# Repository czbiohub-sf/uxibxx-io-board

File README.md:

# uxibxx-io-board
## Introduction
This repository contains the hardware design data, firmware and a Python driver implementation for the UXIB*xx* "family" of digital I/O board~~s~~. This project is intended to provide minimum-friction tools for interfacing Python code to electrical stuff (turning loads on and off, reading switches, etc) in laboratory automation projects.

Currently the device "family" consists of a single example, UXIB-DN12, designed to control a bank of 12 loads such as solenoid valves.

## Directory contents
- `driver/` contains the `uxibxx` Python package used to control UXIB*xx* devices
- `firmware/` contains the source code for the AVR firmware
- `pcb/` contains the KiCAD EDA project files for the UXIB-DN12 PCB

## Getting started
If starting with an already-made UXIB*xx* device, just install the included `uxibxx` package and review the associated API documentation. No extra system-level driver is required on Windows, MacOS or Linux.

See the `README.md` in each subdirectory for further information.

## Licenses
Software source code is licensed under the BSD 3-Clause License. Hardware design files are licensed under CERN-OHL-W.
See the `LICENSE` file in each subdirectory for a copy of the applicable license terms.

## Support
This project is maintained by Greg Courville of the Bioengineering Platform at Chan Zuckerberg Biohub San Francisco.

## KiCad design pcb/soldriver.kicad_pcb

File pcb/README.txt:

This directory has KiCAD 8 source files and other documentation for the UXIB-DN12 valve/relay controller board:

soldriver_sch.pdf            Printable UXIB-DN12 schematic
soldrive_assembly_front.pdf  UXIB-DN12 component placement drawing, front side
soldrive_assembly_back.pdf   UXIB-DN12 component placement drawing, rear side

soldriver.kicad_pro          UXIB-DN12 KiCAD 8 project file
soldriver.kicad_sch          UXIB-DN12 schematic
soldriver.kicad_pcb          UXIB-DN12 PCB layout
footprints.pretty/           Project footprint library
sym/                         Project symbol library

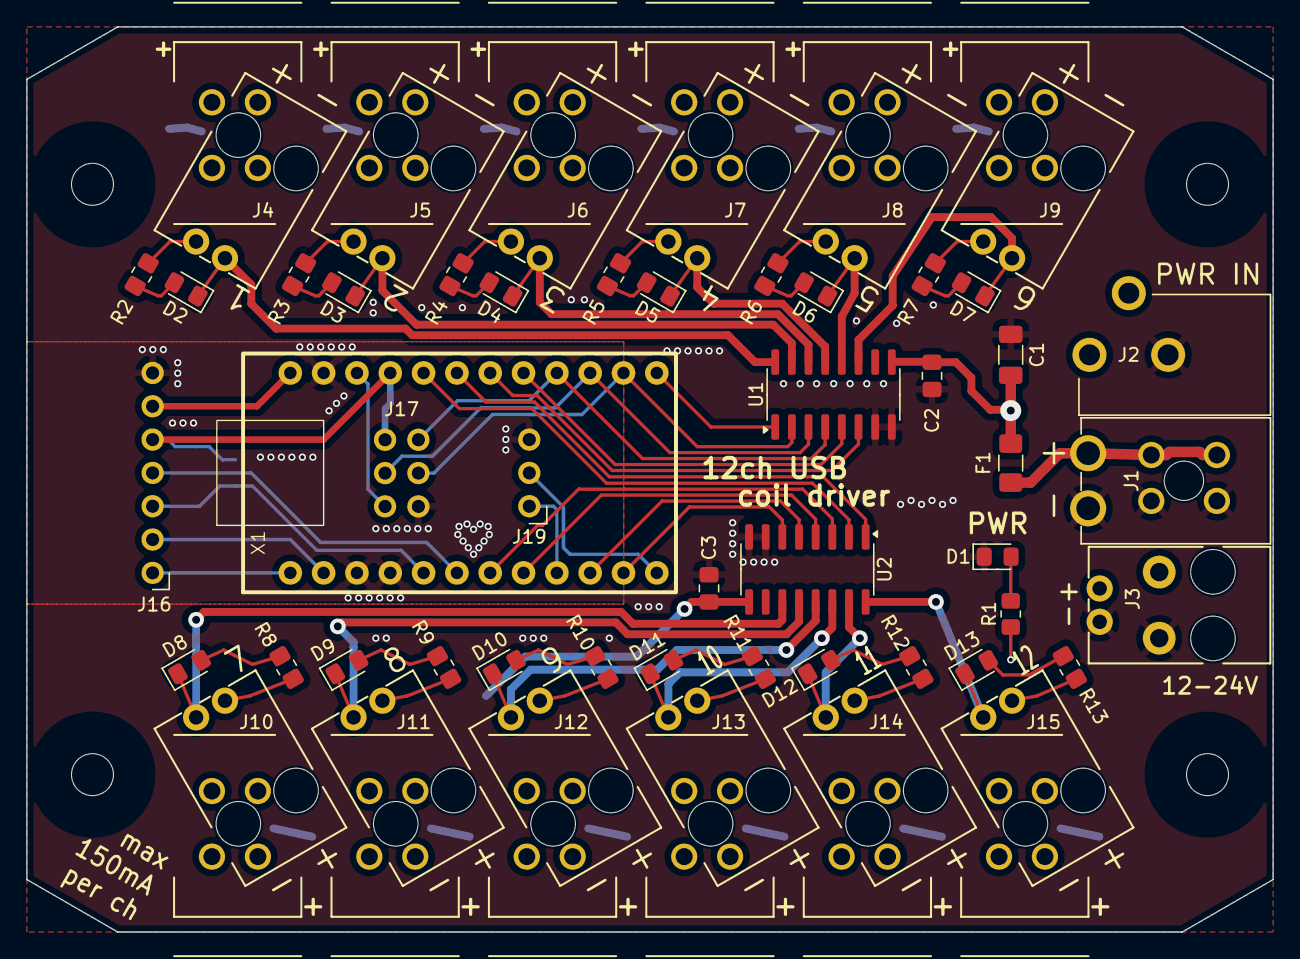
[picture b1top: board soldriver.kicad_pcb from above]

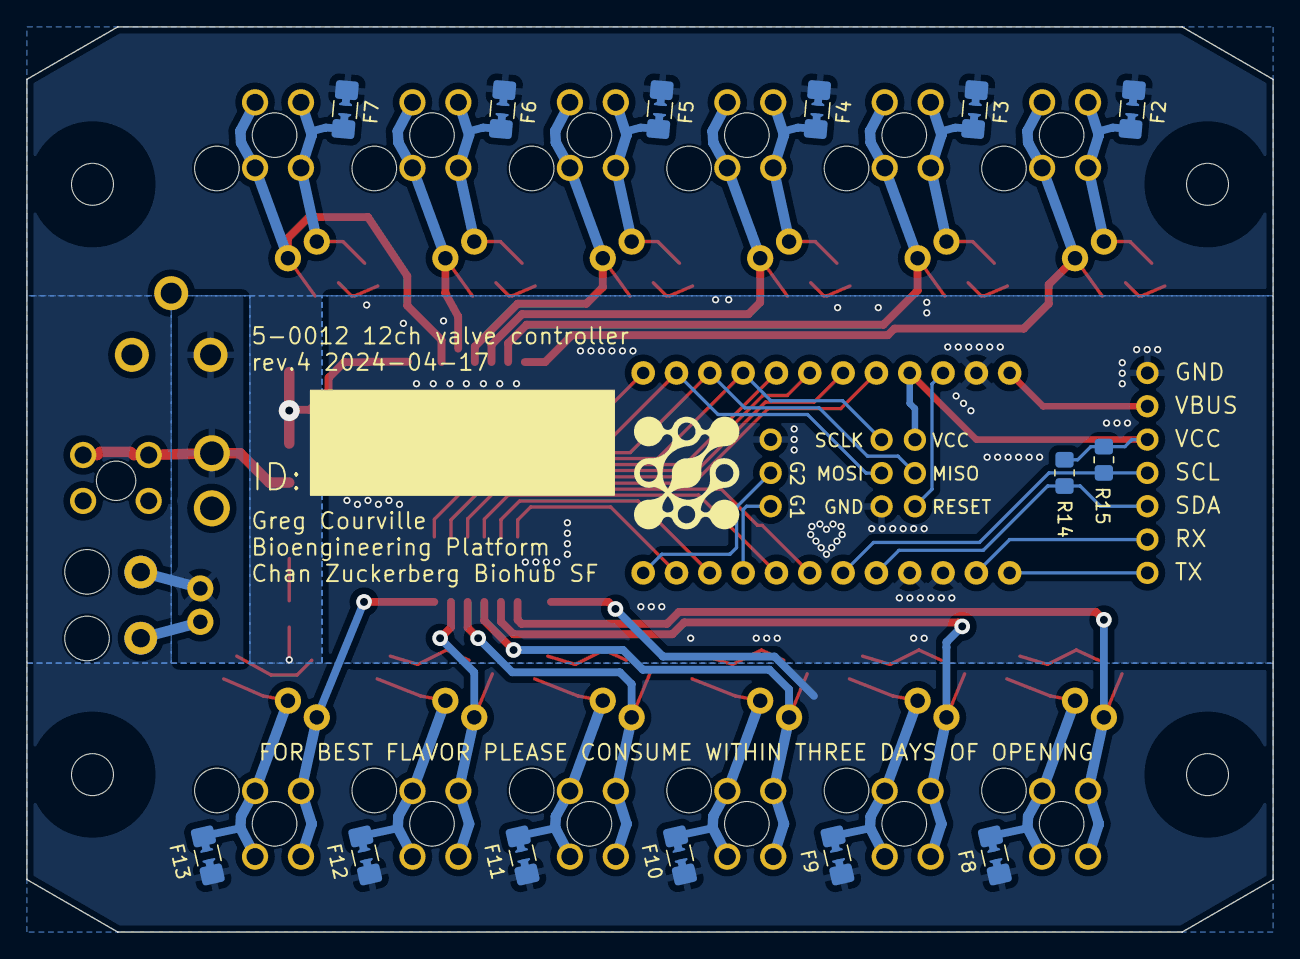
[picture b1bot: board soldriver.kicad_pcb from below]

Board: 2 copper layers, 95.0 x 69.0 mm, 70 parts (14 on the bottom side), 61 nets.

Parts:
C1: 10u; C_1206_3216Metric_Pad1.33x1.80mm_HandSolder
C2, C3: 0.1u; C_0805_2012Metric_Pad1.18x1.45mm_HandSolder
D1, D2, D3, D4, D5, D6, D7, D8, D9, D10, D11, D12, D13: LED; LED_0805_2012Metric_Pad1.15x1.40mm_HandSolder
F1: 2.5A; Fuse_1206_3216Metric_Pad1.42x1.75mm_HandSolder
F2, F3, F4, F5, F6, F7, F8, F9, F10, F11, F12, F13: Polyfuse; fuse_1206_jumperable
J1: 1726480102; CON_1726480102
J2: Barrel_Jack_Switch; CUI_PJ-102AH_with3dmodel
J3: 1726480102; molex_705510001_or_2pos_5mm_tb
J4, J5, J6, J7, J8, J9: 705510001; molex_705510001_or_wago_2601-1102_lh
J10, J11, J12, J13, J14, J15: 705510001; molex_705510001_or_wago_2601-1102_rh
J16: Conn_01x08_Pin; PinHeader_1x07_P2.54mm_Horizontal
J17: Conn_01x08_Pin; PinHeader_2x03_P2.54mm_Vertical
J18: 2601-1102; CONN_2601-1102_WAG
J19: Conn_01x03_Pin; PinHeader_1x03_P2.54mm_Vertical
MH1, MH2, MH3, MH4: MountingHole_3.2mm_M3
R1, R2, R3, R4, R5, R6, R7, R8, R9, R10, R11, R12, R13, R14, R15: 10k; R_0805_2012Metric_Pad1.20x1.40mm_HandSolder
U1, U2: TPL7407LA; SOIC-16_3.9x9.9mm_P1.27mm
X1: promicro_in_socket

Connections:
+24V: C1.1, C2.1, C3.1, F1.1, F2.1, F3.1, F4.1, F5.1, F6.1, F7.1, F8.1, F9.1, F10.1, F11.1, F12.1, F13.1, R1.1, U1.9 (COM), U2.9 (COM)
/CH1: U1.1 (I1), X1.13 (D10/A10)
/CH2: J17.4, U1.2 (I2), X1.14 (D16/MOSI)
/CH3: J17.3, U1.3 (I3), X1.15 (D14/MISO)
/CH4: J17.2, U1.4 (I4), X1.16 (D15/SCLK)
/CH5: U1.5 (I5), X1.17 (D18/A0)
/CH6: U1.6 (I6), X1.18 (D19/A1)
/CH7: U2.6 (I6), X1.11 (D8/A8)
/CH8: U2.5 (I5), X1.10 (D7)
/CH9: U2.4 (I4), X1.8 (D5)
/CH10: U2.3 (I3), X1.7 (D4/A6)
/CH11: U2.2 (I2), X1.20 (D21/A3)
/CH12: U2.1 (I1), X1.19 (D20/A2)
/GP1: J19.1, X1.9 (D6/A7)
/GP2: J19.2, X1.12 (D9/A9)
/O1H: F2.2, J4.1, R2.1
/O2H: F3.2, J5.1, R3.1
/O3H: F4.2, J6.1, R4.1
/O4H: F5.2, J7.1, R5.1
/O5H: F6.2, J8.1, R6.1
/O6H: F7.2, J9.1, R7.1
/O7H: F8.2, J10.1, R8.1
/O8H: F9.2, J11.1, R9.1
/O9H: F10.2, J12.1, R10.1
/O10H: F11.2, J13.1, R11.1
/O11H: F12.2, J14.1, R12.1
/O12H: F13.2, J15.1, R13.1
/OUT1: D2.1 (K), J4.2, U1.16 (O1)
/OUT2: D3.1 (K), J5.2, U1.15 (O2)
/OUT3: D4.1 (K), J6.2, U1.14 (O3)
/OUT4: D5.1 (K), J7.2, U1.13 (O4)
/OUT5: D6.1 (K), J8.2, U1.12 (O5)
/OUT6: D7.1 (K), J9.2, U1.11 (O6)
/OUT7: D8.1 (K), J10.2, U2.11 (O6)
/OUT8: D9.1 (K), J11.2, U2.12 (O5)
/OUT9: D10.1 (K), J12.2, U2.13 (O4)
/OUT10: D11.1 (K), J13.2, U2.14 (O3)
/OUT11: D12.1 (K), J14.2, U2.15 (O2)
/OUT12: D13.1 (K), J15.2, U2.16 (O1)
/RESET: J17.5, X1.22 (!RST)
/RX: J16.2, X1.2 (D0/RX)
/SCL: J16.4, R15.1, X1.6 (D3/SCL)
/SDA: J16.3, R14.1, X1.5 (D2/SDA)
/TX: J16.1, X1.1 (D1/TX)
/VBUS: J16.6, X1.24 (RAW)
/VCC: J16.5, J17.1, R14.2, R15.2, X1.21 (VCC)
GND: C1.2, C2.2, C3.2, D1.1 (K), J1.2, J2.2, J3.2, J16.7, J17.6, J18.1_1, J18.1_2, J19.3, U1.7 (I7), U1.8 (GND), U2.7 (I7), U2.8 (GND), X1.3 (GND), X1.4 (GND), X1.23 (GND)
unnamed: D1.2 (A), R1.2
unnamed: D2.2 (A), R2.2
unnamed: D3.2 (A), R3.2
unnamed: D4.2 (A), R4.2
unnamed: D5.2 (A), R5.2
unnamed: D6.2 (A), R6.2
unnamed: D7.2 (A), R7.2
unnamed: D8.2 (A), R8.2
unnamed: D9.2 (A), R9.2
unnamed: D10.2 (A), R10.2
unnamed: D11.2 (A), R11.2
unnamed: D12.2 (A), R12.2
unnamed: D13.2 (A), R13.2
unnamed: F1.2, J1.1, J2.1, J3.1, J18.2_1, J18.2_2

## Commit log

2024-05-30 test script typo
2024-05-30 formatting
2024-05-30 missing break;
2024-05-30 added EEPROM parameter storage & serial number
2024-05-30 fixed reset-to-bootloader behavior & USB serial number desc now generated from same string as IDN command returns
2024-05-30 change temp io assignments to not touch LEDs
2024-05-30 makefile formatting
2024-05-30 actual i/o assignments for DN12 board
2024-05-30 minor touchups
2024-05-30 add support for string args
2024-05-30 added PCB files
2024-05-30 .gitignore formatting
2024-05-30 add TLS, TCP, IDN(placeholder)
2024-05-30 flesh out gpio.c api more
2024-05-30 err code for unimplemented commands
2024-05-30 i/o commands working
2024-05-30 implement proper cmd lookup & parsing
2024-05-30 .gitignore
2024-05-30 dfu command working, working on arg parsing
2024-05-30 initial fw with LED blinking and skeleton for CDC ACM comms
2024-05-30 change default serial to INITME
2024-05-30 comment out test script
2024-05-30 missing declaration
2024-05-30 add Python driver
2024-05-30 add LICENSE files for driver and fw
2024-05-30 LICENSE files will go in subdirs due to mixed hw/sw repo
2024-05-30 setup.py
2024-05-30 remove lingering 'Fbibxx...' names
2024-05-30 add __all__
2024-05-30 README
2024-05-30 add pyserial dependency
2024-05-30 top LICENSE file
2024-06-13 refactor into a package and add docstrings
2024-06-14 migrate setup metadata to pyproject.toml
2024-06-18 add hardware enumeration/selection functionality; flesh out docstrings
2024-06-18 add Sphinx docs
2024-06-25 fix typehint
2024-06-25 document usb_vidpid arg
2024-06-25 kwargs passthrough
2024-06-25 add usb_vidpid arg to open_first_device()
2024-06-25 add README for Python driver
2024-06-26 fill in top level README
2024-06-26 add license info for pcb
2024-06-27 add LUFA-210130 as submodule
2024-06-28 cleanup
2024-06-28 package version
2024-10-08 switch to 2.2uF tantalum cap
2025-01-28 formatting, comments
2025-01-28 mstick interface
2025-01-28 track changes to headers each source file depends on
2025-01-30 add close()
2025-02-05 protect GPIO-set operation when mixing calls from normal and interrupt context
2025-02-05 pragma onces
2025-02-06 fix CDC notification endpoint size
2025-05-27 update DN12 schematic title block and add PDF
2025-05-27 add front and back component placement drawings
